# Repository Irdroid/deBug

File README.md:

# deBug
printf style debugging Adapter and C library for WCH CH551, CH552, CH554 microcontrollers

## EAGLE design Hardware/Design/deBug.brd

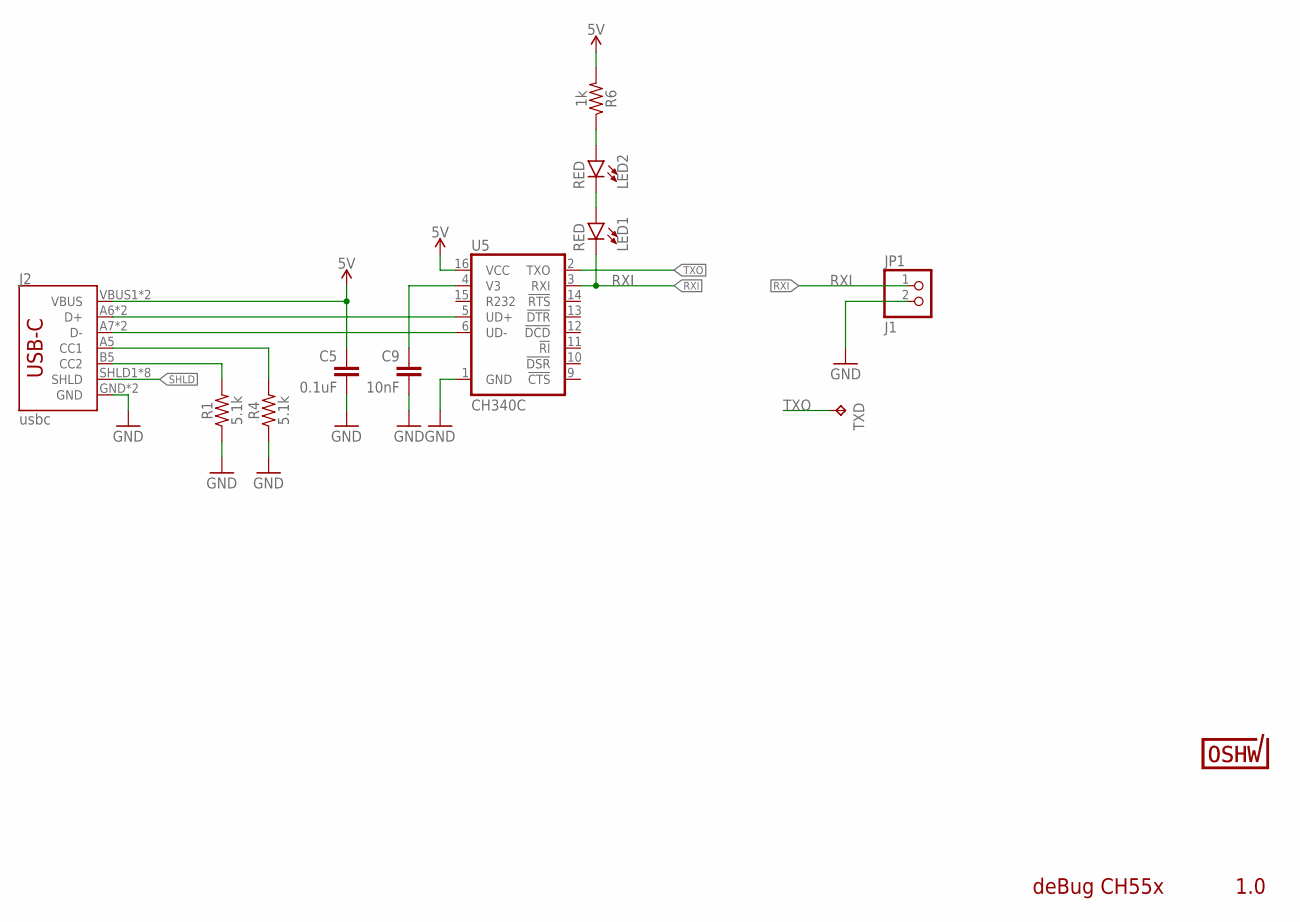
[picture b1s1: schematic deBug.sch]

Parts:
C5: 0.1uF; 0603
C9: 10nF; 0603
J2: usbc; USB-C-16P
JP1: J1; 1X02
LED1, LED2: RED; LED-0603
R1, R4: 5.1k; 0603
R6: 1k; 0603
TXD: TPB1,27; B1,27
U5: CH340C; SO016
U$2: CERT-LARGE; CERT-LARGE-SILK

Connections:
5V: C5.1, J2.VBUS1 (VBUS), J2.VBUS2 (VBUS), R6.2, U5.16 (VCC)
CC1: J2.A5 (CC1), R4.2
CC2: J2.B5 (CC2), R1.2
D+: J2.A6 (D+), J2.B6 (D+), U5.5 (UD+)
D-: J2.A7 (D-), J2.B7 (D-), U5.6 (UD-)
GND: C5.2, C9.2, J2.GND, J2.GND2 (GND), JP1.2, R1.1, R4.1, U5.1 (GND)
unnamed: C9.1, U5.4 (V3)
unnamed: LED2.A, R6.1
unnamed: LED1.A, LED2.C
RXI: JP1.1, LED1.C, U5.3 (RXI)
SHLD: J2.SHLD1 (SHLD), J2.SHLD2 (SHLD), J2.SHLD3 (SHLD), J2.SHLD4 (SHLD), J2.SHLD5 (SHLD), J2.SHLD6 (SHLD), J2.SHLD7 (SHLD), J2.SHLD8 (SHLD)
TXO: TXD.TP, U5.2 (TXO)

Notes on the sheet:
1.0
deBug CH55x

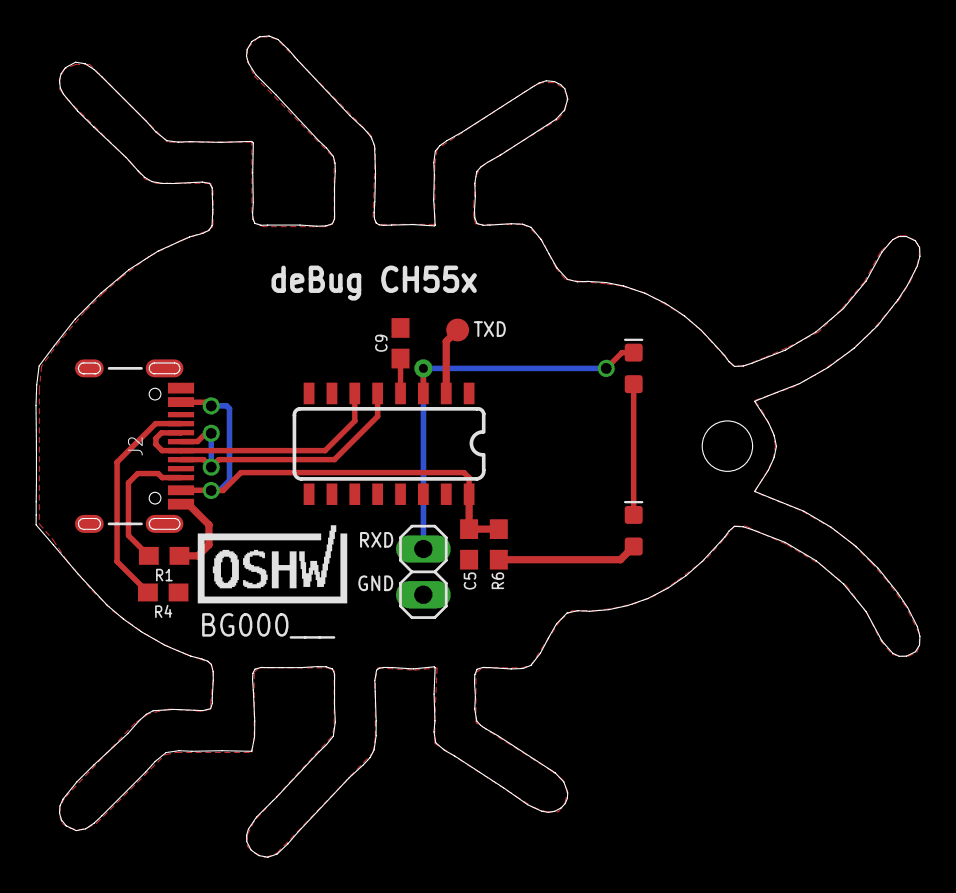
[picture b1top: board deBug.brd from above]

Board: 2 copper layers, 49.1 x 45.6 mm, 13 parts (0 on the bottom side), 12 nets.

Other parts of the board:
U$1: CERT-SMALL-SILK

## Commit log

2025-08-27 Initial commit - Library and demo application
2025-08-29 Added deBug hardware design
2025-08-29 Added pdf schematic
2025-08-29 Added pcb image
2025-08-29 Update Readme.md
    update readme
2025-08-29 Create FUNDING.yml
    Added sponsorship link
2025-09-18 Added debugging adapter pictures
2025-09-18 Added more pictures

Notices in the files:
parts and their libraries:
SparkFun-Capacitors: Licensing: Creative Commons ShareAlike 4.0 International - https://creativecommons.org/licenses/by-sa/4.0
